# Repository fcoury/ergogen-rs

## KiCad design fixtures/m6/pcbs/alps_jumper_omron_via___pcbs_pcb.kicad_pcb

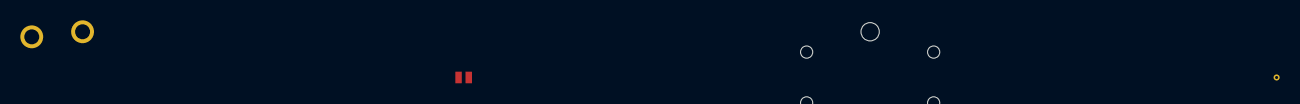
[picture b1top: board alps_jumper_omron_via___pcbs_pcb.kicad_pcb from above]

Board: 2 copper layers, 3 parts (0 on the bottom side), 2 nets, no tracks yet.

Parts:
J1: Jumper
S1: ALPS
S2: OMRON_B3F-4055

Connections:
o_from: S2.1, S2.2
o_to: S2.3, S2.4

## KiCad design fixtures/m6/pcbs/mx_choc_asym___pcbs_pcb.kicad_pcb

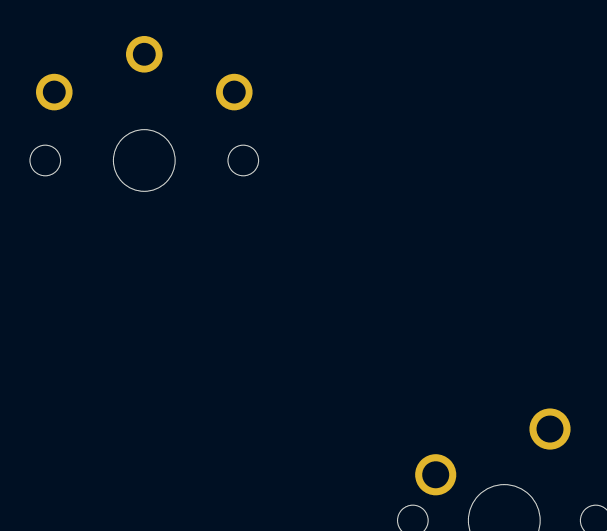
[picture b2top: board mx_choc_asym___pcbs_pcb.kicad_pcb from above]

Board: 2 copper layers, 4 parts (0 on the bottom side), 2 nets, no tracks yet.

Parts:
S1, S3, S4: MX
S2: PG1350

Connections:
net_c: S3.1, S4.1
net_d: S3.2, S4.2

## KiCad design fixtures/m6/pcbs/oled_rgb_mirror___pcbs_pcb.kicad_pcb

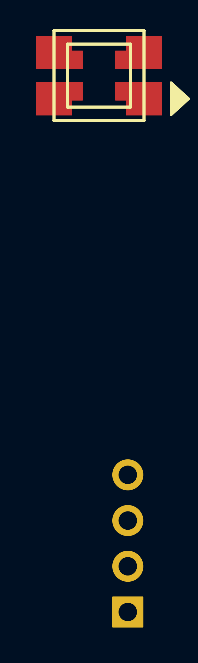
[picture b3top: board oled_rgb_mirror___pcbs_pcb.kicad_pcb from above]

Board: 2 copper layers, 4 parts (0 on the bottom side), 6 nets, no tracks yet.

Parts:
LED1, LED2: WS2812B
OLED1, OLED2: OLED; OLED_headers

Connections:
din: LED1.4, LED1.44, LED2.4, LED2.44
dout: LED1.2, LED1.22, LED2.2, LED2.22
gnd: LED1.3, LED1.33, LED2.3, LED2.33, OLED1.1, OLED2.1
scl: OLED1.3, OLED2.3
sda: OLED1.4, OLED2.4
vcc: LED1.1, LED1.11, LED2.1, LED2.11, OLED1.2, OLED2.2

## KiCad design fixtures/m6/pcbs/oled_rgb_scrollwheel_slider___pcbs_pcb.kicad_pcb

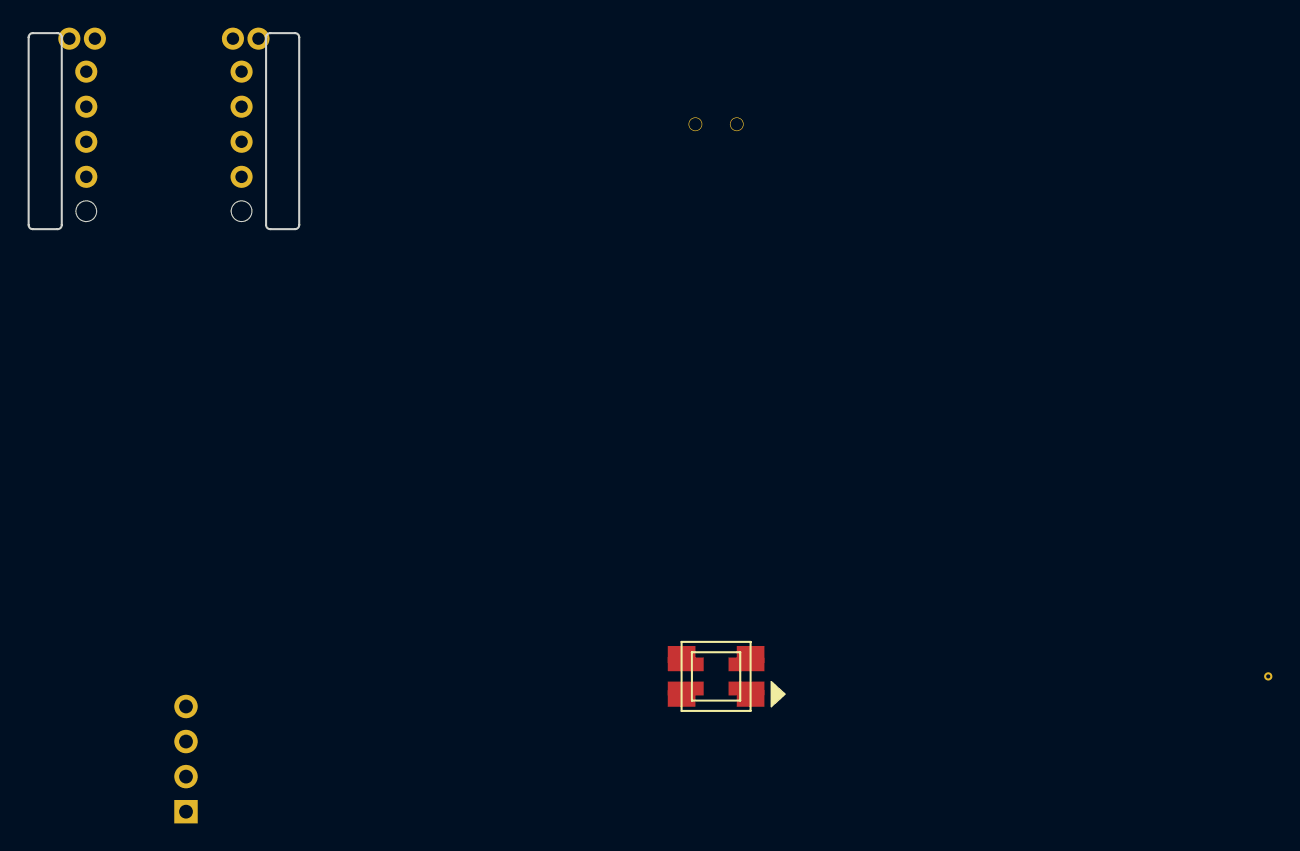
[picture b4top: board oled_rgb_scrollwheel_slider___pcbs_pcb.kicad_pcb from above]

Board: 2 copper layers, 3 parts (0 on the bottom side), 4 nets, no tracks yet.

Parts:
LED1: WS2812B
OLED1: OLED; OLED_headers
T1: SPDT_C128955

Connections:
din: LED1.4, LED1.44
dout: LED1.2, LED1.22
gnd: LED1.3, LED1.33, OLED1.1
vcc: LED1.1, LED1.11, OLED1.2

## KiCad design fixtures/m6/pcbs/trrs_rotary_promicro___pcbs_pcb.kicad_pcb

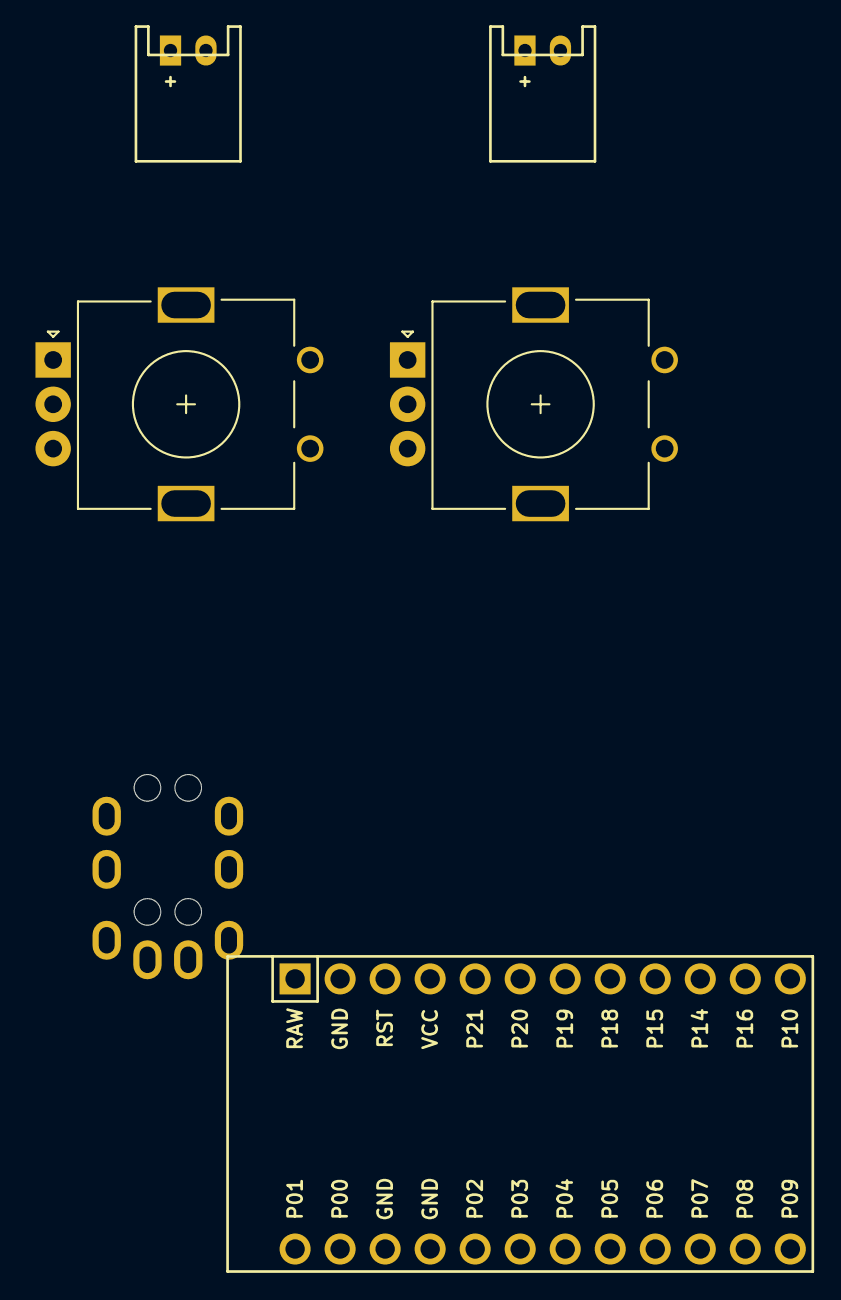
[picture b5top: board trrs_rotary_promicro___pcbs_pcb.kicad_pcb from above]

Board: 2 copper layers, 6 parts (0 on the bottom side), 8 nets, no tracks yet.

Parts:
JST1, JST2: JST_PH_S2B-PH-K_02x2.00mm_Angled
MCU1: ProMicro
ROT1, ROT2: rotary_encoder
TRRS1: TRRS-PJ-320A-dual

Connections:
gnd: MCU1.2, MCU1.15, MCU1.16
n: JST1.2, JST2.2
p: JST1.1, JST2.1
ra: ROT1.A, ROT2.A
rb: ROT1.B, ROT2.B
rc: ROT1.C, ROT2.C
rf: ROT1.1, ROT2.1
rt: ROT1.2, ROT2.2
